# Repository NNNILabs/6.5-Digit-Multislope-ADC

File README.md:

# 6.5 Digit Multislope ADC
## Analog to digital converter than can resolve voltages down to 10uV

#### About

The multislope topology fits comfortably between dual-slope and delta-sigma methods - very few precision components are needed to get very good results. Multislope is a charge balancing method - the input voltage is converted to a current (through the input resistor, one side of which is a virtual ground) and fed continuously into the integrator, and positive and negative reference voltages (which are converted to currents in the same way) are periodically injected into the integrator to maintain net zero charge. This is made possible using a clocked zero crossing comparator which determines which reference is to be switched into the inetgrator every clock cycle. 

This ADC has all the basic parts needed to operate it as a standalone +/-10V digitizer - an LM399 voltage reference, ref amps that convert the reference voltage to +/-10V, an input multiplexer, an input buffer, and the basic multislope components - a resistor network, an analog switch, a composite integrator, a fast comparator and a D latch. Using the on-board jumpers, this board can be configured to run in the "free-running" state (which can be considered a rudimentary delta-sigma method) and in PWM mode, with a constant number of switch transitions of remove errors due to analog switch charge injection.

Each measurement is taken over one power line cycle for normal mode rejection. The input is integrated over 6000 PWM cycles in 50Hz land and 5000 PWM cycles in 60Hz land. One power line cycle integration time gives around 16 bits resolution, 15 PLC is needed to achieve full 6.5 digits.

Each measurement cycle begins with "desaturation, which reads the comparator and slews the integrator to zero. Then the required number of PWM cycles are integrated, followed by rundown to read integrator residue. 

#### Statistics

-to be added-

#### Errata

- D Latch outputs are reversed if you want to use the ADC in free-running mode, luckily this can be changed easily by crossing over wires on the jumpers
- For the present PWM PIO code, the D latch has to be removed and the MEAS and SW-S3 pins have to be bridged together

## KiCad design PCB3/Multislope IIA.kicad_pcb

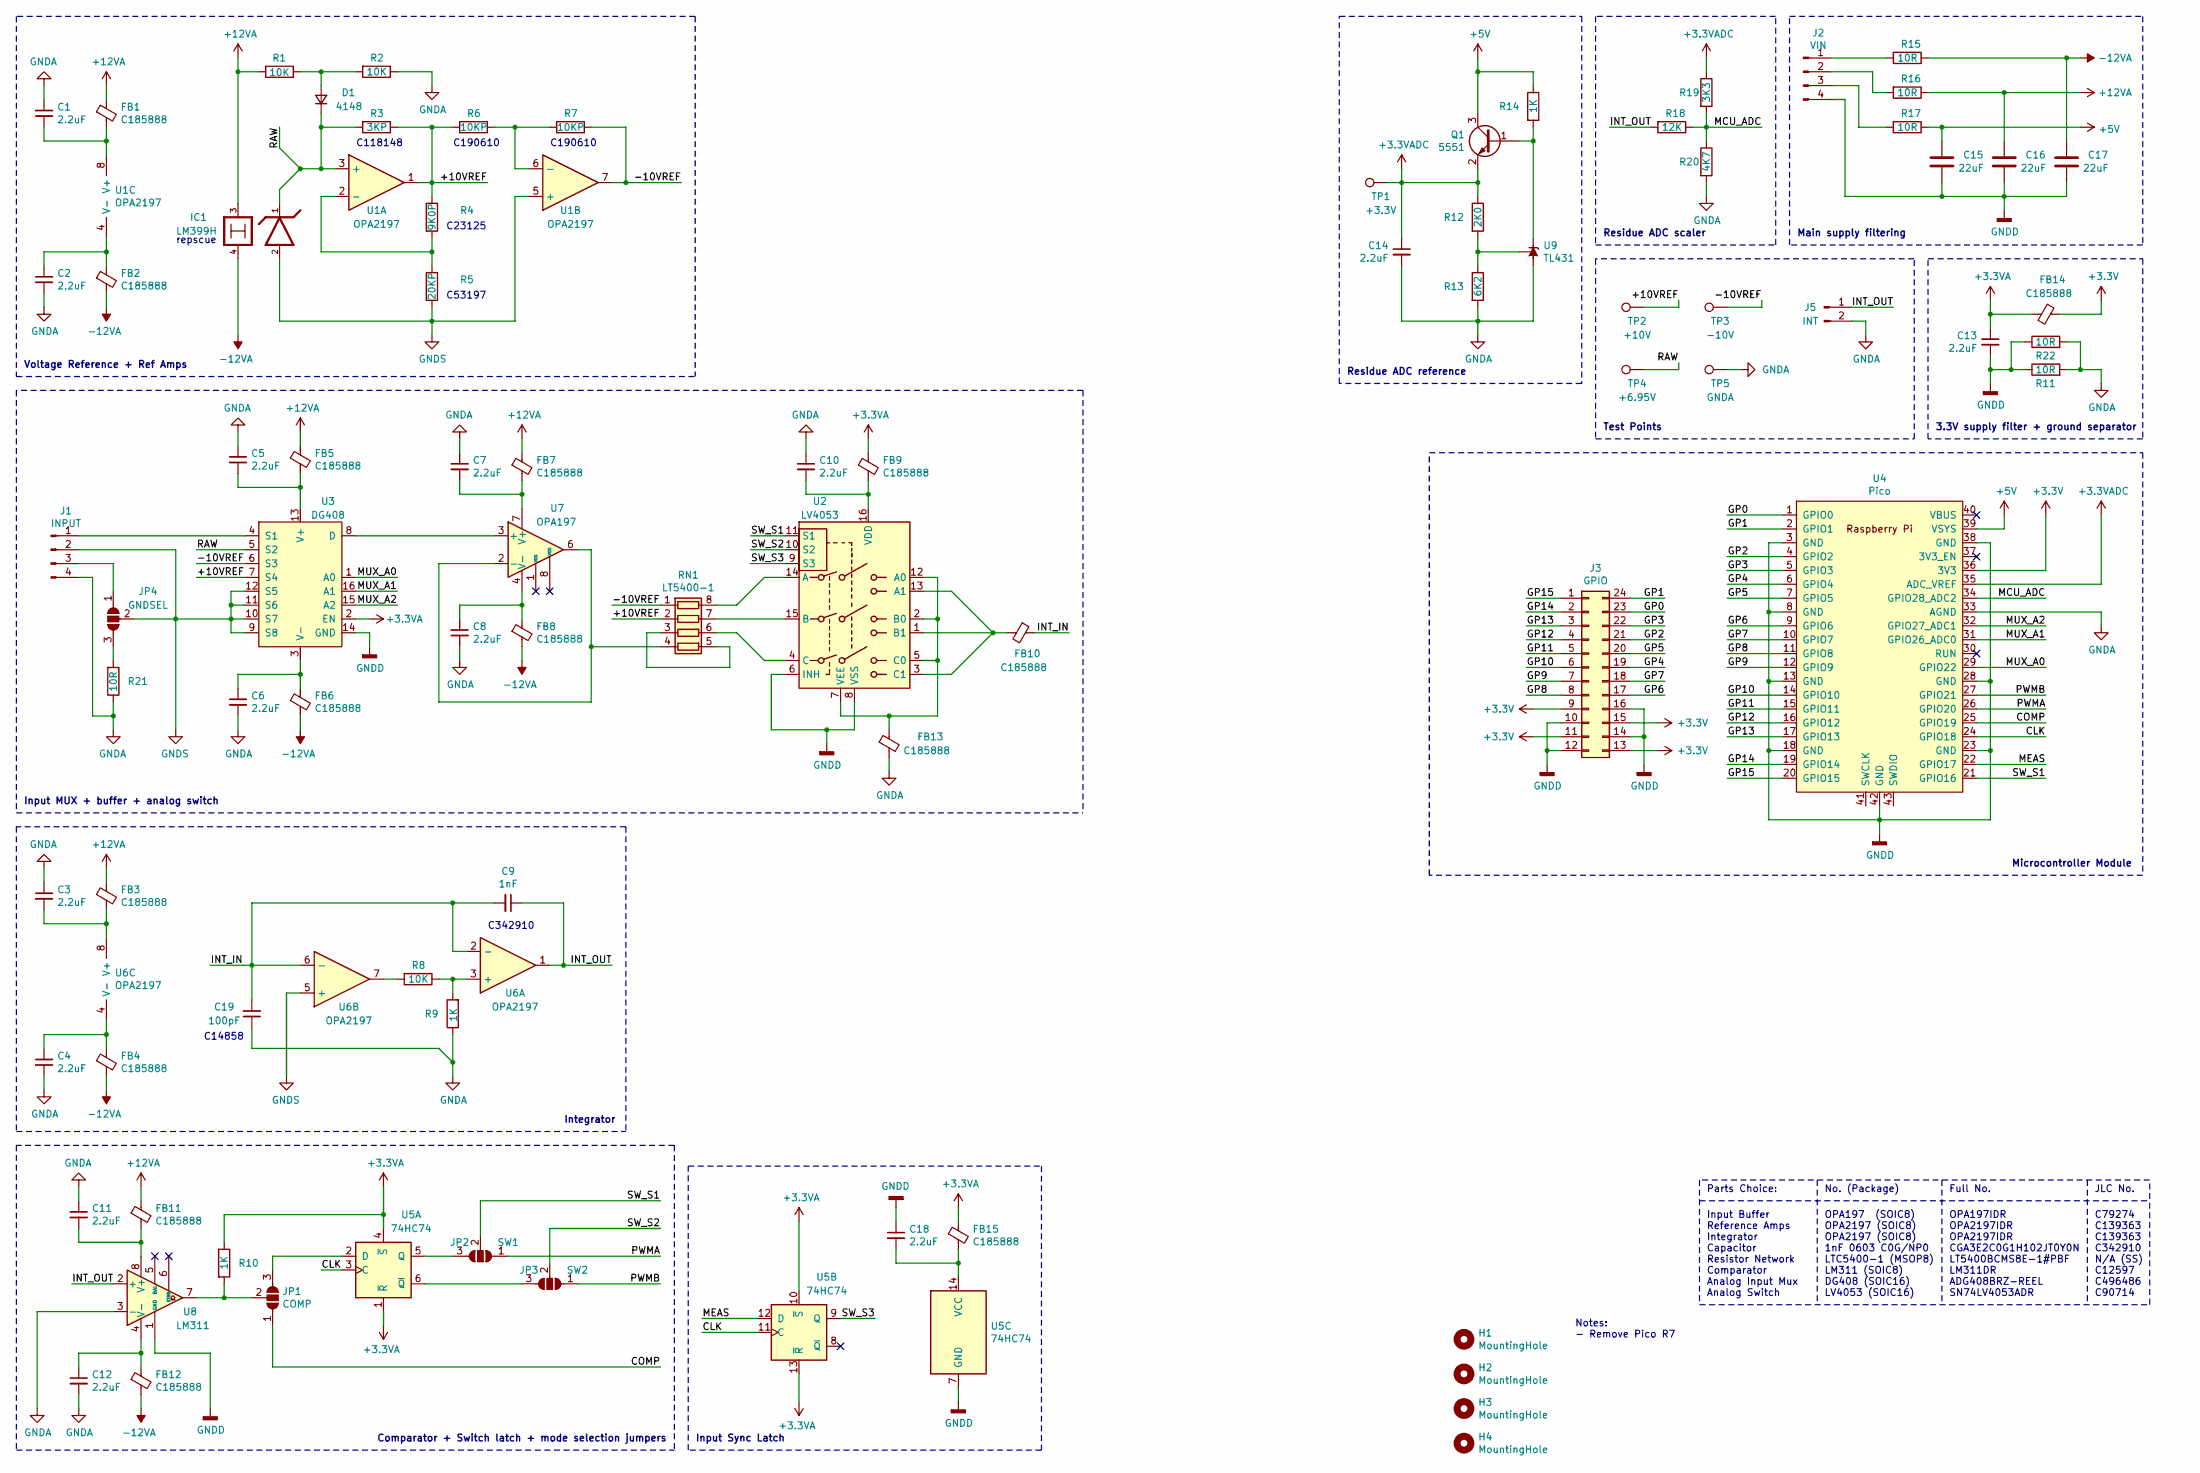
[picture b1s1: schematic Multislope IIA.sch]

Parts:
C1, C2, C3, C4, C5, C6, C7, C8, C10, C11, C12, C13, C14, C18: 2.2uF; C_0603_1608Metric
C9: 1nF; C_0603_1608Metric
C15, C16, C17: 22uF; C_0603_1608Metric
C19: 100pF; C_0603_1608Metric
D1: 4148; D_SOD-323
FB1, FB2, FB3, FB4, FB5, FB6, FB7, FB8, FB9, FB10, FB11, FB12, FB13, FB14, FB15: C185888; L_0603_1608Metric
H1, H2, H3, H4: MountingHole; MountingHole_3mm_Pad_Via
IC1: LM399H; TO-46-4
J1: INPUT; PinHeader_1x04_P2.54mm_Vertical
J2: VIN; PinHeader_1x04_P2.54mm_Vertical
J3: GPIO; PinHeader_2x12_P2.54mm_Vertical
J5: INT; PinHeader_1x02_P1.27mm_Vertical
JP1: COMP; SolderJumper-3_P1.3mm_Open_Pad1.0x1.5mm
JP2: SW1; SolderJumper-3_P1.3mm_Open_Pad1.0x1.5mm
JP3: SW2; SolderJumper-3_P1.3mm_Open_Pad1.0x1.5mm
JP4: GNDSEL; SolderJumper-3_P1.3mm_Open_Pad1.0x1.5mm
Q1: 5551; SOT-23
R1, R2, R8: 10K; R_0603_1608Metric
R3: 3KP; R_0603_1608Metric
R4: 9K0P; R_0603_1608Metric
R5: 20KP; R_0603_1608Metric
R6, R7: 10KP; R_0603_1608Metric
R9, R10, R14: 1K; R_0603_1608Metric
R11, R15, R16, R17, R21, R22: 10R; R_0603_1608Metric
R12: 2K0; R_0603_1608Metric
R13: 6K2; R_0603_1608Metric
R18: 12K; R_0603_1608Metric
R19: 3K3; R_0603_1608Metric
R20: 4K7; R_0603_1608Metric
RN1: LT5400-1; MSOP-8-1EP_3x3mm_P0.65mm_EP1.68x1.88mm
TP1: +3.3V; TestPoint_Pad_D1.0mm
TP2: +10V; TestPoint_Pad_D1.0mm
TP3: -10V; TestPoint_Pad_D1.0mm
TP4: +6.95V; TestPoint_Pad_D1.0mm
TP5: GNDA; TestPoint_Pad_D1.0mm
U1, U6: OPA2197; SOIC-8_3.9x4.9mm_P1.27mm
U2: LV4053; SOIC-16_3.9x9.9mm_P1.27mm
U3: DG408; SOIC-16_3.9x9.9mm_P1.27mm
U4: Pico; RPi_Pico_SMD_TH
U5: 74HC74; SOIC-14_3.9x8.7mm_P1.27mm
U7: OPA197; SOIC-8_3.9x4.9mm_P1.27mm
U8: LM311; SOIC-8_3.9x4.9mm_P1.27mm
U9: TL431; SOT-23

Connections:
+3.3VA: C13.1, FB9.1, FB14.2, FB15.1, R10.1, U3.2 (EN), U5.1 (~R), U5.4 (~S), U5.10 (~S), U5.13 (~R)
+3.3VADC: C14.1, Q1.2 (E), R12.1, R19.1, TP1.1, U4.35 (ADC_VREF)
+3V3: FB14.1, J3.9, J3.11, J3.13, J3.15, U4.36 (3V3)
+5V: C15.1, Q1.3 (C), R14.1, R17.1, U4.39 (VSYS)
+12VA: C16.1, FB1.1, FB3.1, FB5.1, FB7.1, FB11.1, IC1.3, R1.1, R16.1
-12VA: C17.1, FB2.2, FB4.2, FB6.2, FB8.2, FB12.2, IC1.4, R15.1
/+10VREF: R3.1, R4.1, R6.2, RN1.2 (R2.1), TP2.1, U1.1, U3.7 (S4)
/-10VREF: R7.1, RN1.1 (R1.1), TP3.1, U1.7, U3.6 (S3)
/CLK: U4.24 (GPIO18), U5.3 (C), U5.11 (C)
/COMP: JP1.1 (A), U4.25 (GPIO19)
/GP0: J3.23, U4.1 (GPIO0)
/GP1: J3.24, U4.2 (GPIO1)
/GP2: J3.21, U4.4 (GPIO2)
/GP3: J3.22, U4.5 (GPIO3)
/GP4: J3.19, U4.6 (GPIO4)
/GP5: J3.20, U4.7 (GPIO5)
/GP6: J3.17, U4.9 (GPIO6)
/GP7: J3.18, U4.10 (GPIO7)
/GP8: J3.8, U4.11 (GPIO8)
/GP9: J3.7, U4.12 (GPIO9)
/GP10: J3.6, U4.14 (GPIO10)
/GP11: J3.5, U4.15 (GPIO11)
/GP12: J3.4, U4.16 (GPIO12)
/GP13: J3.3, U4.17 (GPIO13)
/GP14: J3.2, U4.19 (GPIO14)
/GP15: J3.1, U4.20 (GPIO15)
/INT_IN: C9.2, C19.2, FB10.1, U6.2 (-), U6.6 (-)
/INT_OUT: C9.1, J5.1, R18.2, U6.1, U8.2 (+)
/MCU_ADC: R18.1, R19.2, R20.1, U4.34 (GPIO28_ADC2)
/MEAS: U4.22 (GPIO17), U5.12 (D)
/MUX_A0: U3.1 (A0), U4.29 (GPIO22)
/MUX_A1: U3.16 (A1), U4.31 (GPIO26_ADC0)
/MUX_A2: U3.15 (A2), U4.32 (GPIO27_ADC1)
/PWMA: JP2.1 (A), U4.26 (GPIO20)
/PWMB: JP3.1 (A), U4.27 (GPIO21)
/RAW: D1.1 (K), IC1.1, R3.2, TP4.1, U1.3 (+), U3.5 (S2)
/SW_S1: JP2.2 (C), U2.11 (S1), U4.21 (GPIO16)
/SW_S2: JP3.2 (C), U2.10 (S2)
/SW_S3: U2.9 (S3), U5.9 (Q)
GNDA: C1.1, C2.2, C3.1, C4.2, C5.1, C6.2, C7.1, C8.2, C10.1, C11.1, C12.2, C14.2, C19.1, FB13.2, J1.4, J5.2, R2.1, R9.1, R11.2, R13.2, R20.2, R21.1, R22.2, TP5.1, U4.33 (AGND), U8.3 (-), U9.3 (A)
GNDD: C13.2, C15.2, C16.2, C17.2, C18.1, J2.4, J3.10, J3.12, J3.14, J3.16, R11.1, R22.1, U2.6 (INH), U2.8 (VSS), U3.14 (GND), U4.3 (GND), U4.8 (GND), U4.13 (GND), U4.18 (GND), U4.23 (GND), U4.28 (GND), U4.38 (GND), U4.42 (GND), U5.7 (GND), U8.1 (GND)
GNDS: IC1.2, J1.2, JP4.2 (C), R5.2, U1.5 (+), U3.9 (S8), U3.10 (S7), U3.11 (S6), U3.12 (S5), U6.5 (+)
unnamed: C1.2, FB1.2, U1.8 (V+)
unnamed: C2.1, FB2.1, U1.4 (V-)
unnamed: C3.2, FB3.2, U6.8 (V+)
unnamed: C4.1, FB4.1, U6.4 (V-)
unnamed: C5.2, FB5.2, U3.13 (V+)
unnamed: C6.1, FB6.1, U3.3 (V-)
unnamed: C7.2, FB7.2, U7.7 (V+)
unnamed: C8.1, FB8.1, U7.4 (V-)
unnamed: C10.2, FB9.2, U2.16 (VDD)
unnamed: C11.2, FB11.2, U8.8 (V+)
unnamed: C12.1, FB12.1, U8.4 (V-)
unnamed: C18.2, FB15.2, U5.14 (VCC)
unnamed: D1.2 (A), R1.2, R2.2
unnamed: FB10.2, U2.1 (B1), U2.3 (C1), U2.13 (A1)
unnamed: FB13.1, U2.2 (B0), U2.5 (C0), U2.7 (VEE), U2.12 (A0)
unnamed: J1.1, U3.4 (S1)
unnamed: J1.3, JP4.1 (A)
unnamed: J2.1, R15.2
unnamed: J2.2, R16.2
unnamed: J2.3, R17.2
unnamed: JP1.2 (C), R10.2, U8.7
unnamed: JP1.3 (B), U5.2 (D)
unnamed: JP2.3 (B), U5.5 (Q)
unnamed: JP3.3 (B), U5.6 (~Q)
unnamed: JP4.3 (B), R21.2
unnamed: Q1.1 (B), R14.2, U9.1 (K)
unnamed: R4.2, R5.1, U1.2 (-)
unnamed: R6.1, R7.2, U1.6 (-)
unnamed: R8.1, R9.2, U6.3 (+)
unnamed: R8.2, U6.7
unnamed: R12.2, R13.1, U9.2 (REF)
unnamed: RN1.3 (R3.1), RN1.5 (R4.2)
unnamed: RN1.4 (R4.1), U7.2 (-), U7.6
unnamed: RN1.6 (R3.2), U2.4 (C)
unnamed: RN1.7 (R2.2), U2.15 (B)
unnamed: RN1.8 (R1.2), U2.14 (A)
unnamed: U3.8 (D), U7.3 (+)

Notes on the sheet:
C23125
C53197
C118148
Input Buffer Reference Amps Integrator Capacitor Resistor Network Comparator Analog Input Mux Analog Switch
OPA197 (SOIC8) OPA2197 (SOIC8) OPA2197 (SOIC8) 1nF 0603 C0G/NP0 LTC5400-1 (MSOP8) LM311 (SOIC8) DG408 (SOIC16) LV4053 (SOIC16)
OPA197IDR OPA2197IDR OPA2197IDR CGA3E2C0G1H102JT0Y0N LT5400BCMS8E-1#PBF LM311DR ADG408BRZ-REEL SN74LV4053ADR
C190610
C190610
repscue
C342910
Parts Choice:
C79274 C139363 C139363 C342910 N/A (SS) C12597 C496486 C90714
No. (Package)
Full No.
JLC No.
Notes: - Remove Pico R7
Voltage Reference + Ref Amps
Input MUX + buffer + analog switch
Integrator
Comparator + Switch latch + mode selection jumpers
Main supply filtering
Residue ADC reference
Residue ADC scaler
3.3V supply filter + ground separator
Input Sync Latch
Microcontroller Module
C14858
Test Points

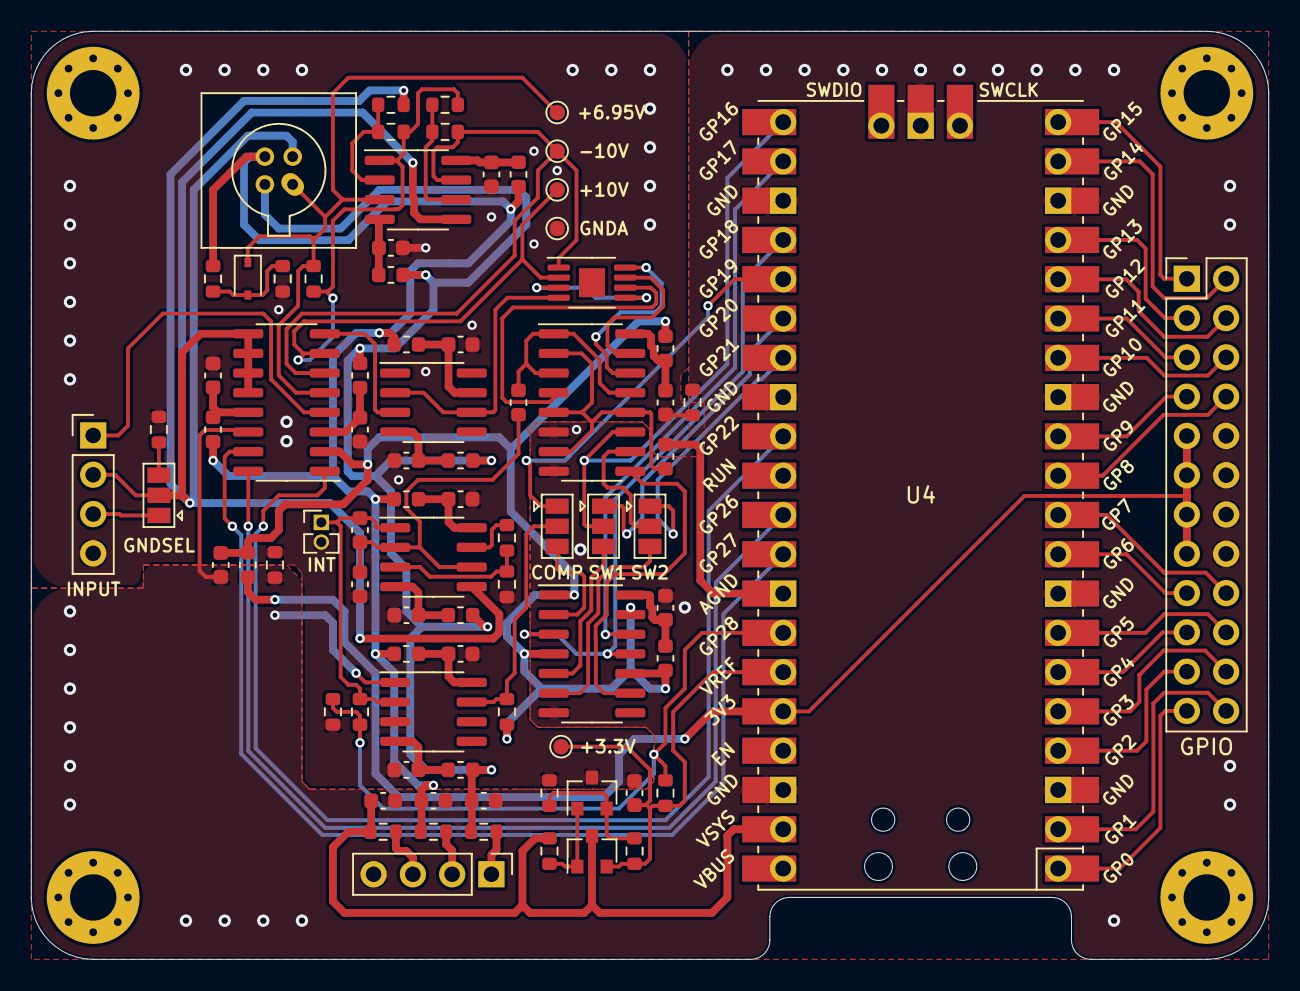
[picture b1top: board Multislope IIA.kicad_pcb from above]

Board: 2 copper layers, 80.0 x 60.0 mm, 86 parts (0 on the bottom side), 79 nets.

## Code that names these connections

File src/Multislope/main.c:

#include <stdio.h>
#include "pico/stdlib.h"
#include "hardware/pio.h"
#include "hardware/clocks.h"
#include "hardware/irq.h"
#include "hardware/adc.h"
#include "hardware/gpio.h"
#include "ms.pio.h"
#define __STDC_FORMAT_MACROS
#include <inttypes.h>

#define MAINS_FREQ 50                   // Hz

const uint8_t MCLK = 18;                // SPI Clock Pin
const uint8_t M_EN = 16;

const uint8_t MUX_A0 = 22;
const uint8_t MUX_A1 = 26;
const uint8_t MUX_A2 = 27;

const uint8_t MEAS = 17;

const uint8_t PWMA = 20;                // need to be next to each other
const uint8_t PWMB = 21;                // need to be next to each other
const uint8_t COMP = 19;

const uint8_t LED_PIN = 0;

const uint8_t RESGP = 28;
const uint8_t RESADC = 2;

const uint64_t mainsPeriodus = 1000000/MAINS_FREQ;

#if MAINS_FREQ == 50
    const uint32_t MScyclesPerPLC = 6000;
#elif MAINS_FREQ == 60
    const uint32_t MScyclesPerPLC = 5000;
#endif

uint32_t rundownCounts = 0;

int64_t get_counts(PIO pio, uint sm , uint32_t countNum){
    uint32_t counts = 0;
    pio_sm_put_blocking(pio, sm, countNum - 1);
    gpio_put(LED_PIN, true);
    counts = ~pio_sm_get_blocking(pio, sm);
    rundownCounts = ~pio_sm_get_blocking(pio, sm);
    gpio_put(LED_PIN, false);
    return ((2*(int64_t)counts) - (int64_t)countNum);
}

int main() {
    //set_sys_clock_khz(128000, true);                    // Set system clock to 128 Mhz to make the PIO clock frequency be evenly divisible by it
    set_sys_clock_khz(96000, true);  
    stdio_init_all();


    gpio_init(MUX_A0);
    gpio_init(MUX_A1);
    gpio_init(MUX_A2);
    gpio_init(MCLK);
    gpio_init(LED_PIN);

    gpio_set_dir(MCLK, GPIO_OUT);
    gpio_set_dir(MUX_A0, GPIO_OUT);
    gpio_set_dir(MUX_A1, GPIO_OUT);
    gpio_set_dir(MUX_A2, GPIO_OUT);
    gpio_set_dir(LED_PIN, GPIO_OUT);
    
    sleep_us(10);
    gpio_put(MCLK, true);
    gpio_put(MUX_A0, false);
    gpio_put(MUX_A1, false);
    gpio_put(MUX_A2, false);

    // Choose PIO instance (0 or 1)
    PIO pio = pio0;

    // Get first free state machine in PIO 0
    uint multislopeSM = pio_claim_unused_sm(pio, true);

    // Add PIO program to PIO instruction memory. SDK will find location and
    // return with the memory offset of the program.
    uint multislopeOffset = pio_add_program(pio, &ms_program);

    const float div = 10;

    // Initialize the program using the helper function in our .pio file
    ms_program_init(pio, multislopeSM, multislopeOffset, PWMA, COMP, div, MEAS);


    // Start running our PIO program in the state machine
    pio_sm_set_enabled(pio, multislopeSM, true);
    



    while (true) {
        uint32_t reqPLCCounts = 1;
        uint32_t requestedCounts = 120000;

        int64_t counts = get_counts(pio, multislopeSM, requestedCounts);
        int64_t finalCount = (14 * (int64_t)counts) + ((int64_t)rundownCounts - 32);
        double volts = 20 * ((double)finalCount/(16 * requestedCounts));
        printf("%fV | counts:%" PRId64 "\n", volts, finalCount);
        //printf("%" PRId64 "\n", finalCount);
        sleep_ms(1000);
    }
    
}

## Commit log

2021-11-14 Hardware files without errors fixed
2021-11-14 added src with set up Cmake
2021-11-14 testing improved multilope algorythm
2021-11-14 correct pin setup added
2021-11-14 fixed complementary PWM bug
2021-11-17 PIO free running mode implemented
2021-11-20 experimental half working reading ADC PIO functionality
2021-11-20 working mulstislope with readout
2021-11-22 backup before IRQ implementation
2021-12-09 semi working interrupt based ADC residue reading
2022-01-10 new PIO code working, moved build folder
2022-01-15 working PIO counts and PWM code
2022-01-20 Added Images
2022-02-01 added NPLC measurements
2022-02-04 rundown startup
2022-02-11 added gitignore for easy building
2022-02-11 added build script
2022-02-11 fixed build script
2022-02-11 fixing gitignore for cmake
2022-02-11 working build script
2022-02-11 updated gitignore
2022-02-16 fixed halting on pre rundown
2022-03-30 Added code
2022-03-30 modified pio
2022-03-30 modified
2022-04-02 desaturation testing
2022-04-03 multislope all parts operational
2022-04-04 added some ADC math
2022-04-06 experimenting with different PLC measurement technique
2022-04-06 removed redundant PLC code
